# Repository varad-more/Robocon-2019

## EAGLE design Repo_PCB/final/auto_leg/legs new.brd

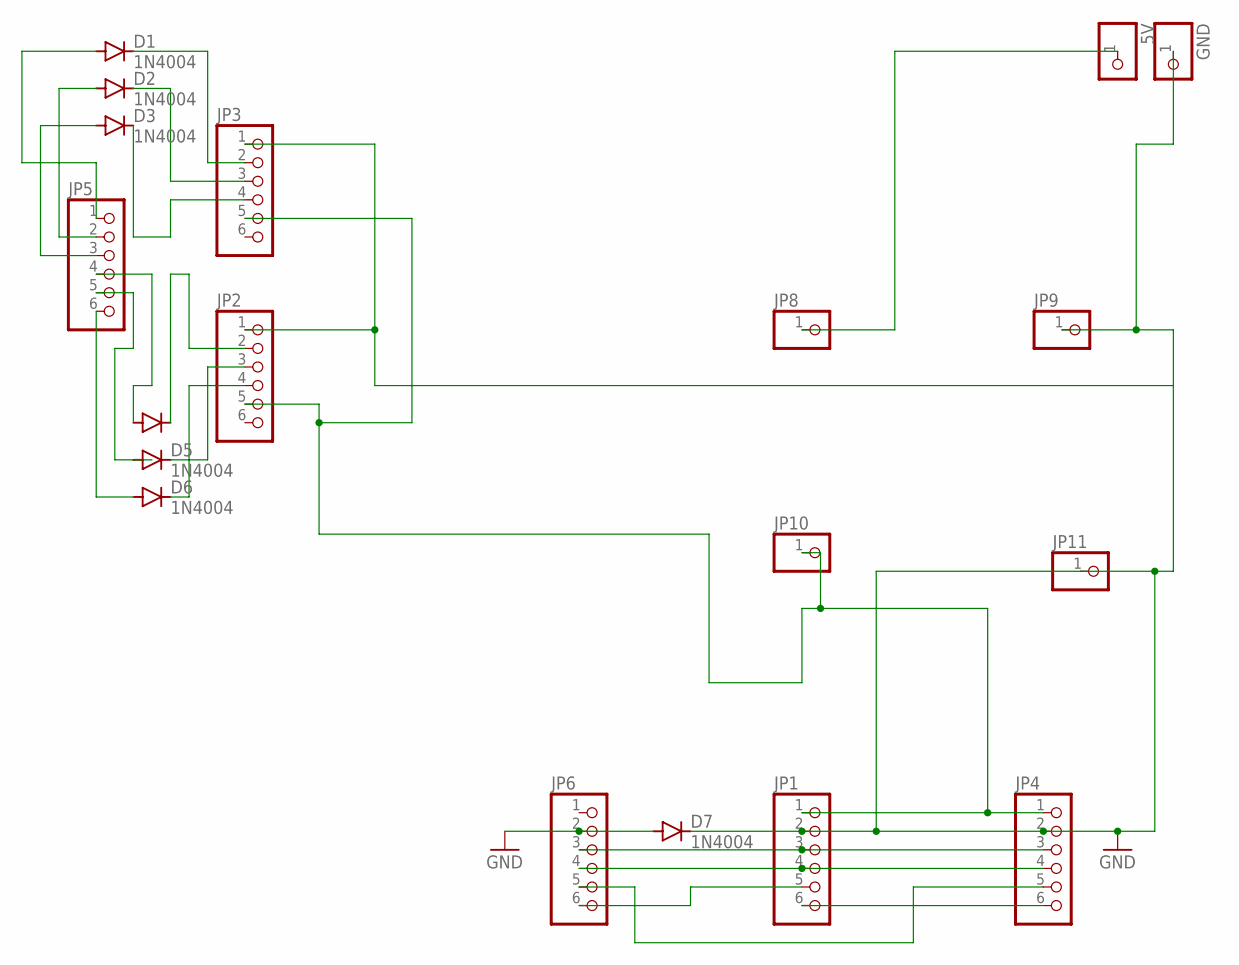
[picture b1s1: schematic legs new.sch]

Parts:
5V: PINHD-1X1; 1X01
D1, D2, D3, D4, D5, D6, D7: 1N4004; DO41-10
GND: PINHD-1X1; 1X01
JP1, JP2, JP3, JP4, JP5, JP6: PINHD-1X6; 1X06
JP8, JP9, JP10, JP11: PINHD-1X1; 1X01

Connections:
GND: D7.A, D7.C, GND.1, JP1.2, JP2.1, JP3.1, JP4.2, JP6.2, JP9.1, JP11.1
unnamed: 5V.1, JP8.1
unnamed: D1.A, JP5.1
unnamed: D2.A, JP5.2
unnamed: JP1.4, JP4.4, JP6.4
unnamed: D3.C, JP3.4
unnamed: JP1.6, JP4.6
unnamed: D4.C, JP2.2
unnamed: D5.A, JP5.5
unnamed: D6.A, JP5.6
unnamed: JP4.5, JP6.5
unnamed: JP1.3, JP4.3, JP6.3
unnamed: JP1.5, JP6.6
unnamed: D4.A, JP5.4
unnamed: D6.C, JP2.4
unnamed: D5.C, JP2.3
unnamed: D1.C, JP3.2
unnamed: D3.A, JP5.3
unnamed: D2.C, JP3.3
VCC: JP1.1, JP2.5, JP3.5, JP4.1, JP10.1

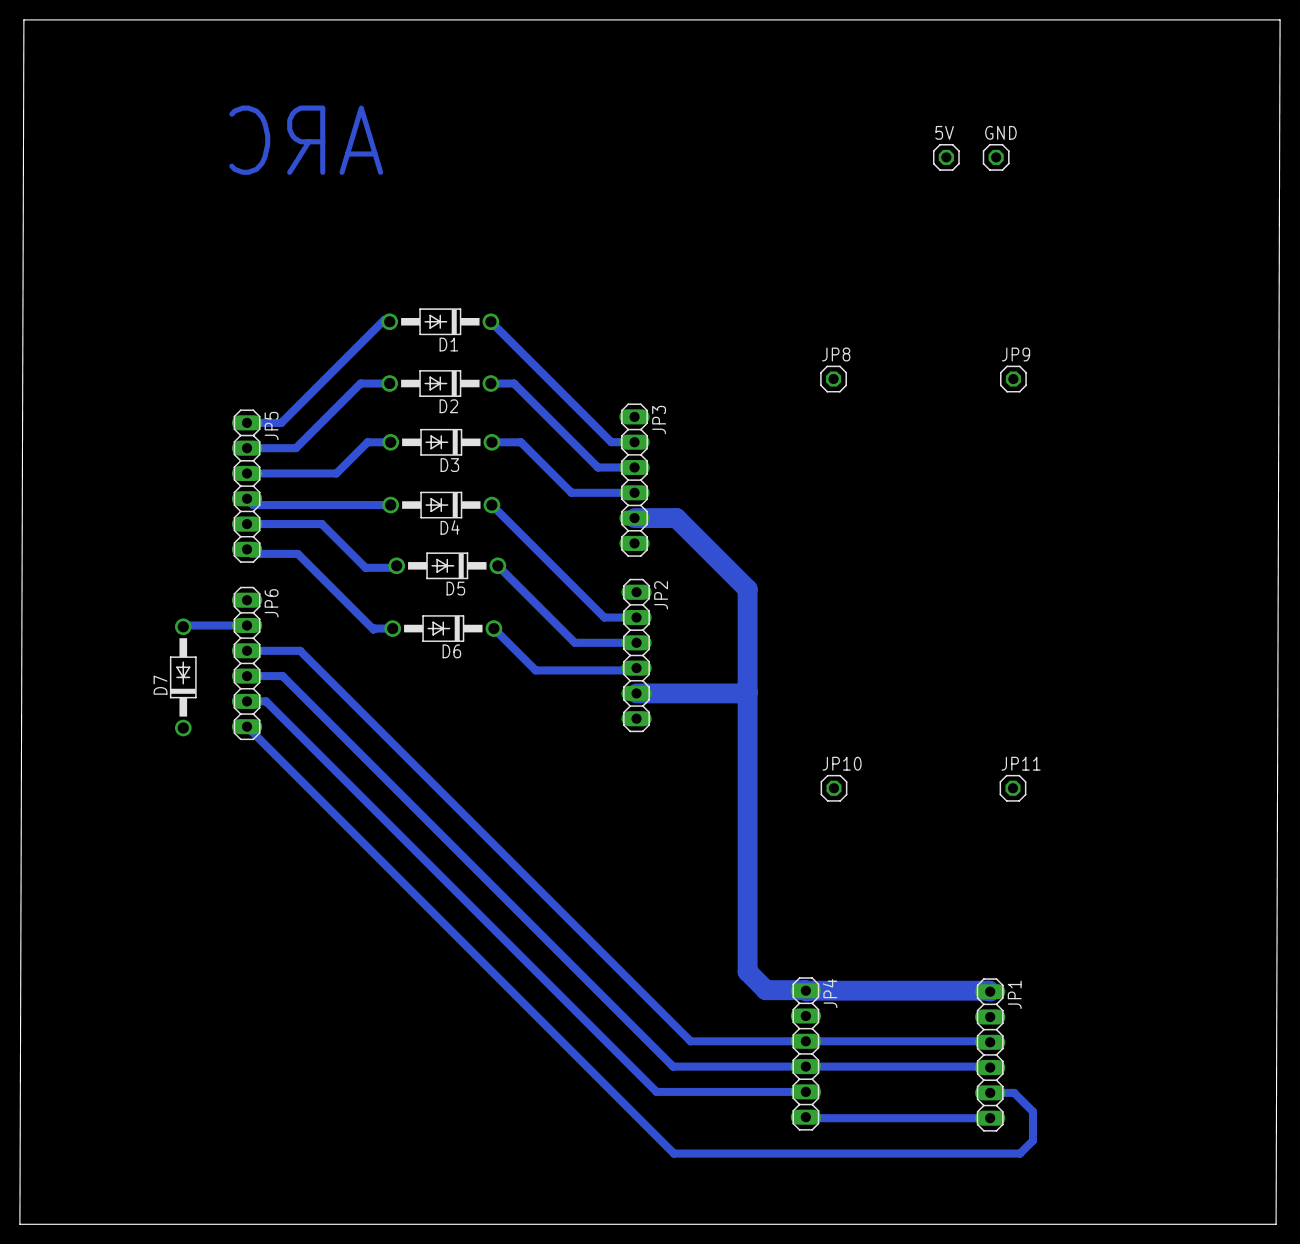
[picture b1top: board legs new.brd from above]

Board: 2 copper layers, 126.5 x 120.9 mm, 19 parts (0 on the bottom side), 20 nets.

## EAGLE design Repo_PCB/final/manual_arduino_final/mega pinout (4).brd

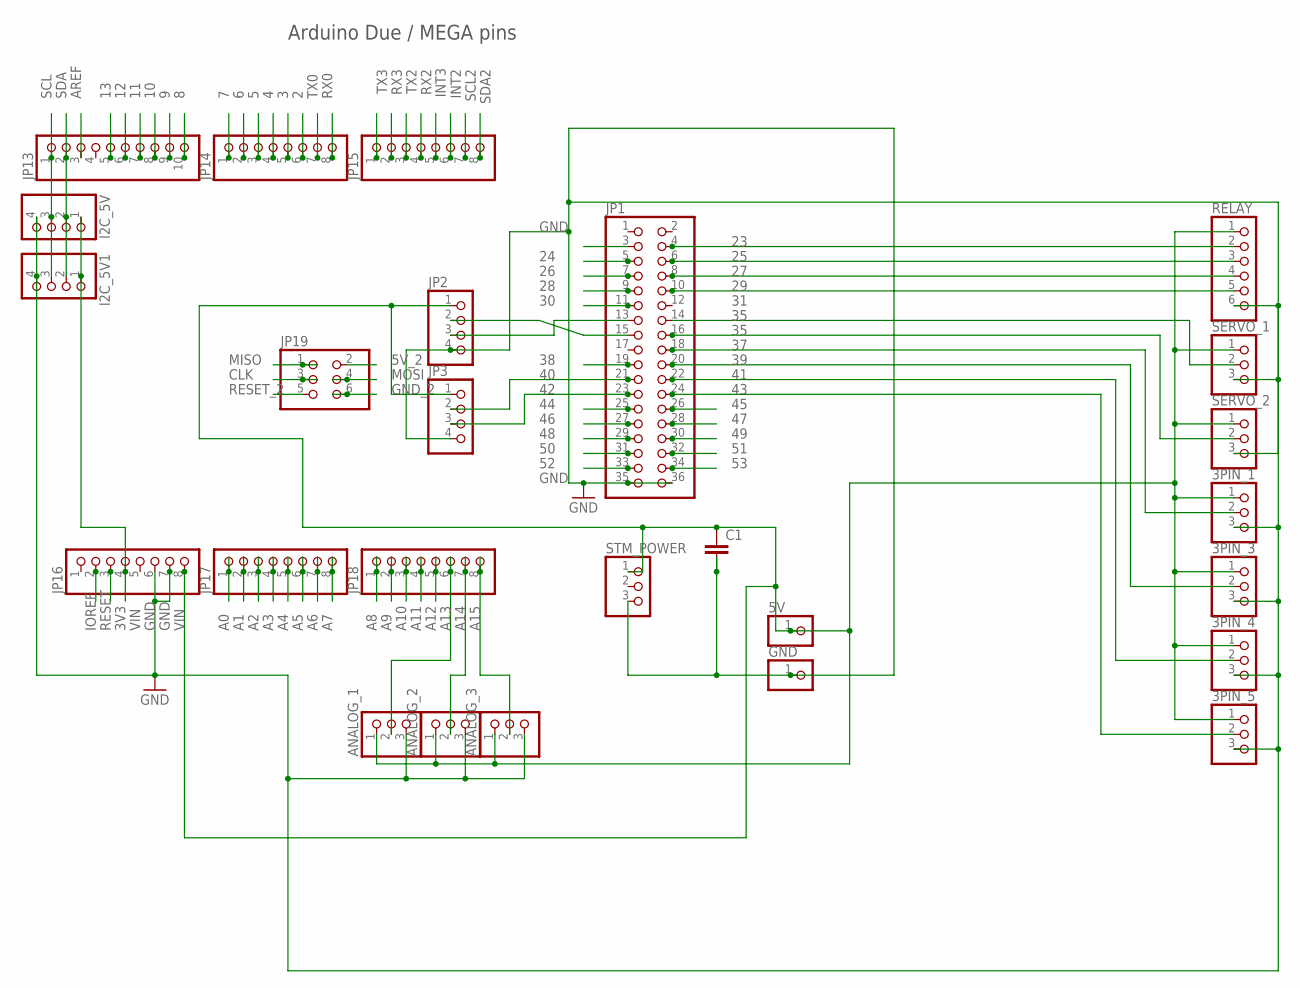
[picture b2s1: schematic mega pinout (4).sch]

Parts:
3PIN_1, 3PIN_3, 3PIN_4, 3PIN_5: PINHD-1X3; 1X03
5V: PINHD-1X1; 1X01
ANALOG_1, ANALOG_2, ANALOG_3: PINHD-1X3; 1X03
C1: C-EU075-032X103; C075-032X103
GND: PINHD-1X1; 1X01
I2C_5V, I2C_5V1: PINHD-1X4; 1X04
JP1: PINHD-2X18; 2X18
JP2, JP3: PINHD-1X4; 1X04
JP13: PINHD-1X10; 1X10
JP14, JP15, JP16, JP17, JP18: PINHD-1X8; 1X08
JP19: PINHD-2X3; 2X03
RELAY: PINHD-1X6; 1X06
SERVO_1, SERVO_2: PINHD-1X3; 1X03
STM_POWER: PINHD-1X3; 1X03

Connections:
2: JP14.6
3: JP14.5
3V3: I2C_5V.1, I2C_5V1.1, JP16.4
4: JP14.4
5: JP14.3
5V_2: JP19.2
6: JP14.2
7: JP14.1
8: JP13.10
9: JP13.9
10: JP13.8
11: JP13.7
12: JP13.6
13: JP13.5
23: JP1.4, RELAY.2
24: JP1.5
25: JP1.6, RELAY.3
26: JP1.7
27: JP1.8, RELAY.4
28: JP1.9
29: JP1.10, RELAY.5
30: JP1.11
31: JP1.14, SERVO_1.2
35: JP1.16, SERVO_2.2
37: 3PIN_1.2, JP1.18
38: JP1.19
39: 3PIN_3.2, JP1.20
40: JP1.21, JP3.2
41: 3PIN_4.2, JP1.22
42: JP1.23, JP3.3
43: 3PIN_5.2, JP1.24
44: JP1.25
45: JP1.26
46: JP1.27
47: JP1.28
48: JP1.29
49: JP1.30
50: JP1.31
51: JP1.32
52: JP1.33
53: JP1.34
A0: JP17.1
A1: JP17.2
A2: JP17.3
A3: JP17.4
A4: JP17.5
A5: JP17.6
A6: JP17.7
A7: JP17.8
A8: JP18.1
A9: JP18.2
A10: JP18.3
A11: JP18.4
A12: JP18.5
A13: ANALOG_1.2, JP18.6
A14: ANALOG_2.2, JP18.7
A15: ANALOG_3.2, JP18.8
AREF: JP13.3
CLK: JP19.3
GND: 3PIN_1.3, 3PIN_3.3, 3PIN_4.3, 3PIN_5.3, ANALOG_1.3, ANALOG_2.3, ANALOG_3.3, C1.2, GND.1, I2C_5V.4, I2C_5V1.4, JP1.35, JP1.36, JP2.4, JP3.4, JP16.6, JP16.7, RELAY.6, SERVO_1.3, SERVO_2.3, STM_POWER.3
GND_2: JP19.6
INT2: JP15.6
INT3: JP15.5
IOREF: JP16.2
MISO: JP19.1
MOSI: JP19.4
unnamed: JP1.15, JP2.2
unnamed: JP1.13, JP2.3
RESET: JP16.3
RESET_2: JP19.5
RX0: JP14.8
RX2: JP15.4
RX3: JP15.2
SCL: I2C_5V.3, I2C_5V1.3, JP13.1
SCL2: JP15.7
SDA: I2C_5V.2, I2C_5V1.2, JP13.2
SDA2: JP15.8
TX0: JP14.7
TX2: JP15.3
TX3: JP15.1
VIN: 3PIN_1.1, 3PIN_3.1, 3PIN_4.1, 3PIN_5.1, 5V.1, ANALOG_1.1, ANALOG_2.1, ANALOG_3.1, C1.1, JP2.1, JP3.1, JP16.8, RELAY.1, SERVO_1.1, SERVO_2.1, STM_POWER.1

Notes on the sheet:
Arduino Due / MEGA pins

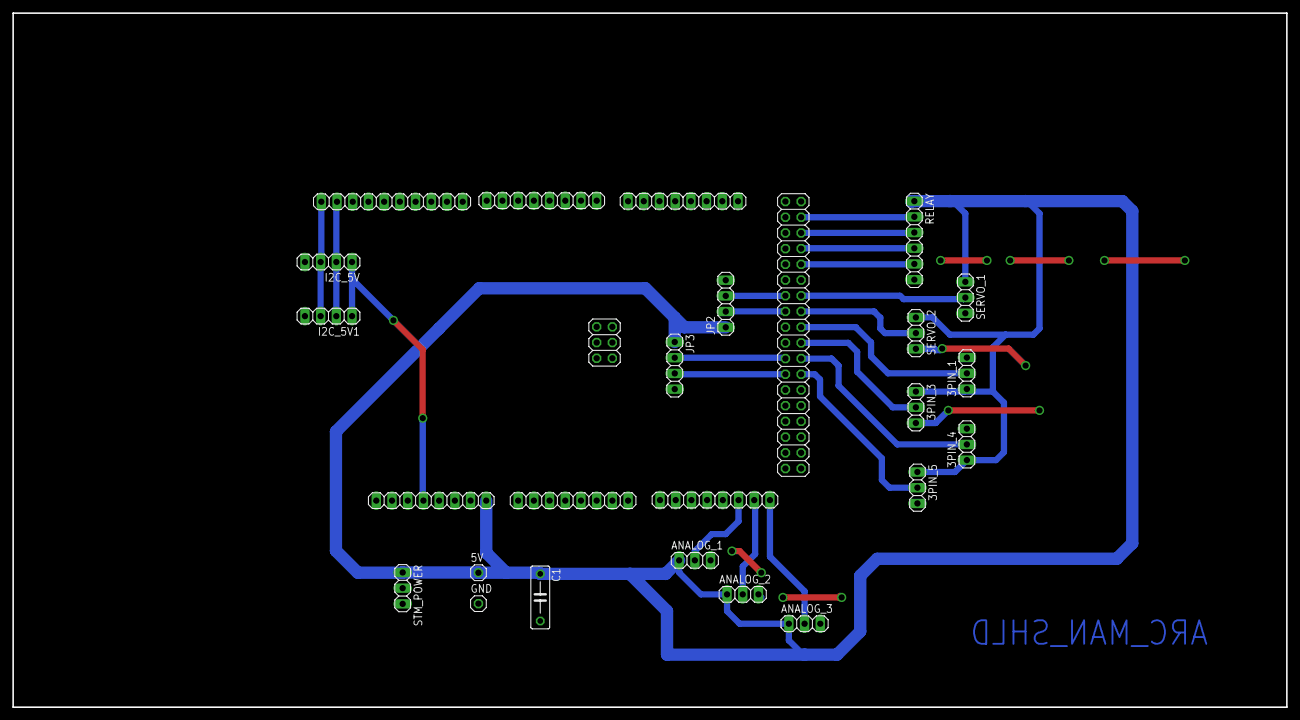
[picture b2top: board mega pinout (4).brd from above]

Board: 2 copper layers, 206.0 x 112.2 mm, 26 parts (0 on the bottom side), 22 nets.

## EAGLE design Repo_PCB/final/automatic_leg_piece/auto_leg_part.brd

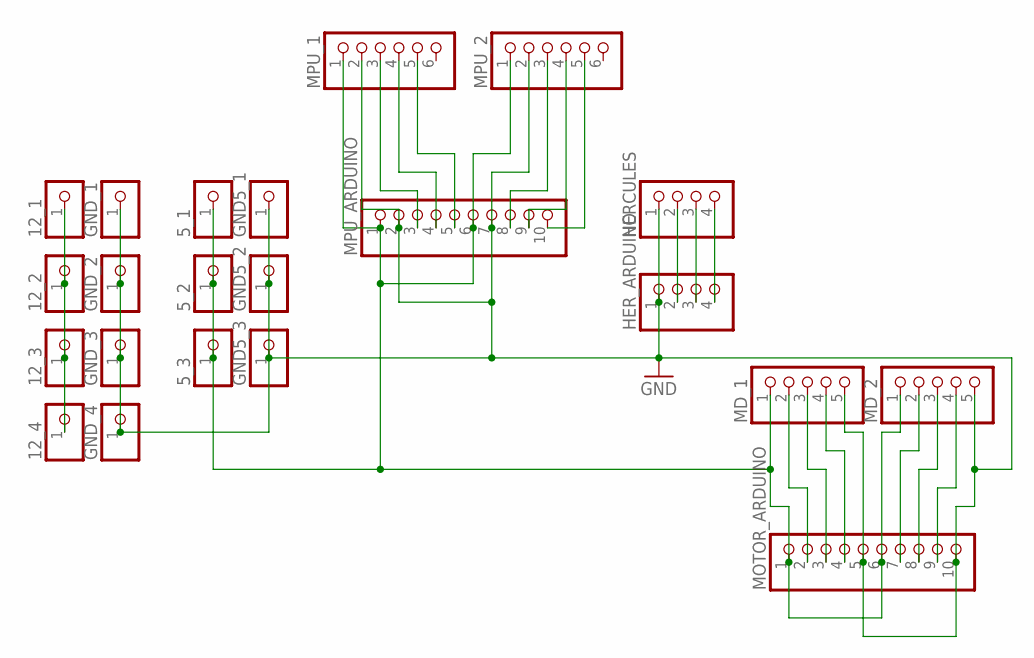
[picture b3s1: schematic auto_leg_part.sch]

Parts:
5_1, 5_2, 5_3, 12_1, 12_2, 12_3, 12_4: PINHD-1X1; 1X01
GND5_1, GND5_2, GND5_3: PINHD-1X1; 1X01
GND_1, GND_2, GND_3, GND_4: PINHD-1X1; 1X01
HERCULES: PINHD-1X4; 1X04
HER_ARDUINO: PINHD-1X4; 1X04
MD_1, MD_2: PINHD-1X5; 1X05
MOTOR_ARDUINO: PINHD-1X10; 1X10
MPU_1, MPU_2: PINHD-1X6; 1X06
MPU_ARDUINO: PINHD-1X10; 1X10

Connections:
GND: GND5_1.1, GND5_2.1, GND5_3.1, GND_1.1, GND_2.1, GND_3.1, GND_4.1, HERCULES.1, HER_ARDUINO.1, MD_1.5, MD_2.5, MOTOR_ARDUINO.5, MOTOR_ARDUINO.10, MPU_1.2, MPU_2.2, MPU_ARDUINO.2, MPU_ARDUINO.7
unnamed: 12_1.1, 12_2.1, 12_3.1, 12_4.1
unnamed: 5_1.1, 5_2.1, 5_3.1, MD_1.1, MD_2.1, MOTOR_ARDUINO.1, MOTOR_ARDUINO.6, MPU_1.1, MPU_2.1, MPU_ARDUINO.1, MPU_ARDUINO.6
unnamed: MPU_1.3, MPU_ARDUINO.3
unnamed: MPU_1.4, MPU_ARDUINO.4
unnamed: MPU_1.5, MPU_ARDUINO.5
unnamed: MPU_2.3, MPU_ARDUINO.8
unnamed: MPU_2.4, MPU_ARDUINO.9
unnamed: MPU_2.5, MPU_ARDUINO.10
unnamed: MD_1.4, MOTOR_ARDUINO.4
unnamed: MD_1.3, MOTOR_ARDUINO.3
unnamed: MD_1.2, MOTOR_ARDUINO.2
unnamed: MD_2.2, MOTOR_ARDUINO.7
unnamed: MD_2.3, MOTOR_ARDUINO.8
unnamed: MD_2.4, MOTOR_ARDUINO.9
unnamed: HERCULES.2, HER_ARDUINO.2
unnamed: HERCULES.3, HER_ARDUINO.3
unnamed: HERCULES.4, HER_ARDUINO.4

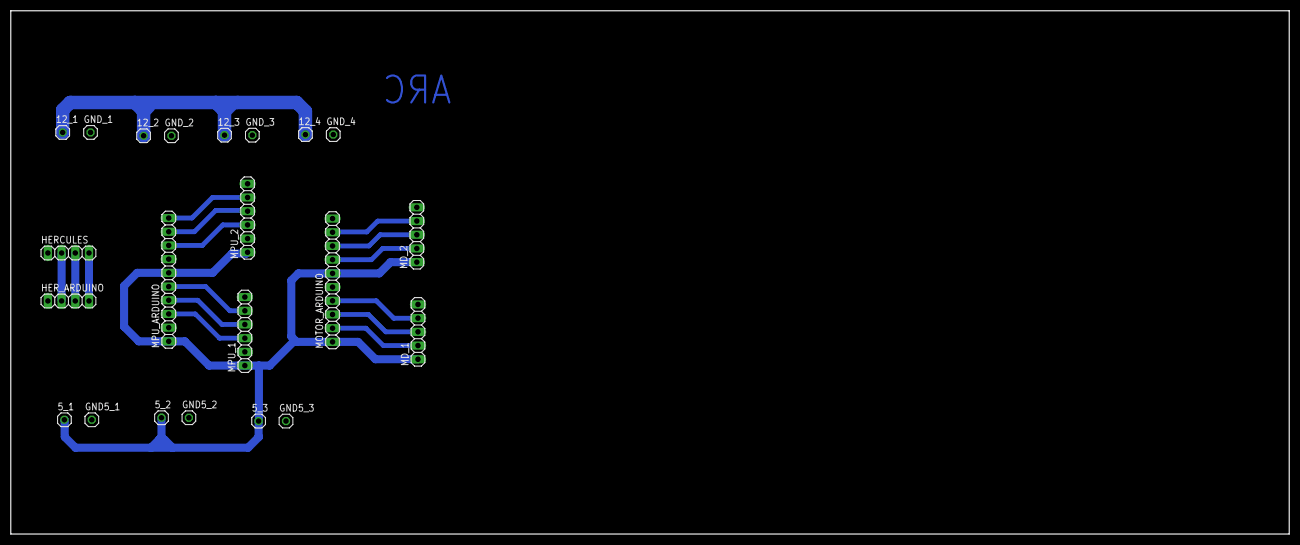
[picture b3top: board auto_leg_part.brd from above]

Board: 2 copper layers, 237.0 x 97.0 mm, 22 parts (0 on the bottom side), 18 nets.

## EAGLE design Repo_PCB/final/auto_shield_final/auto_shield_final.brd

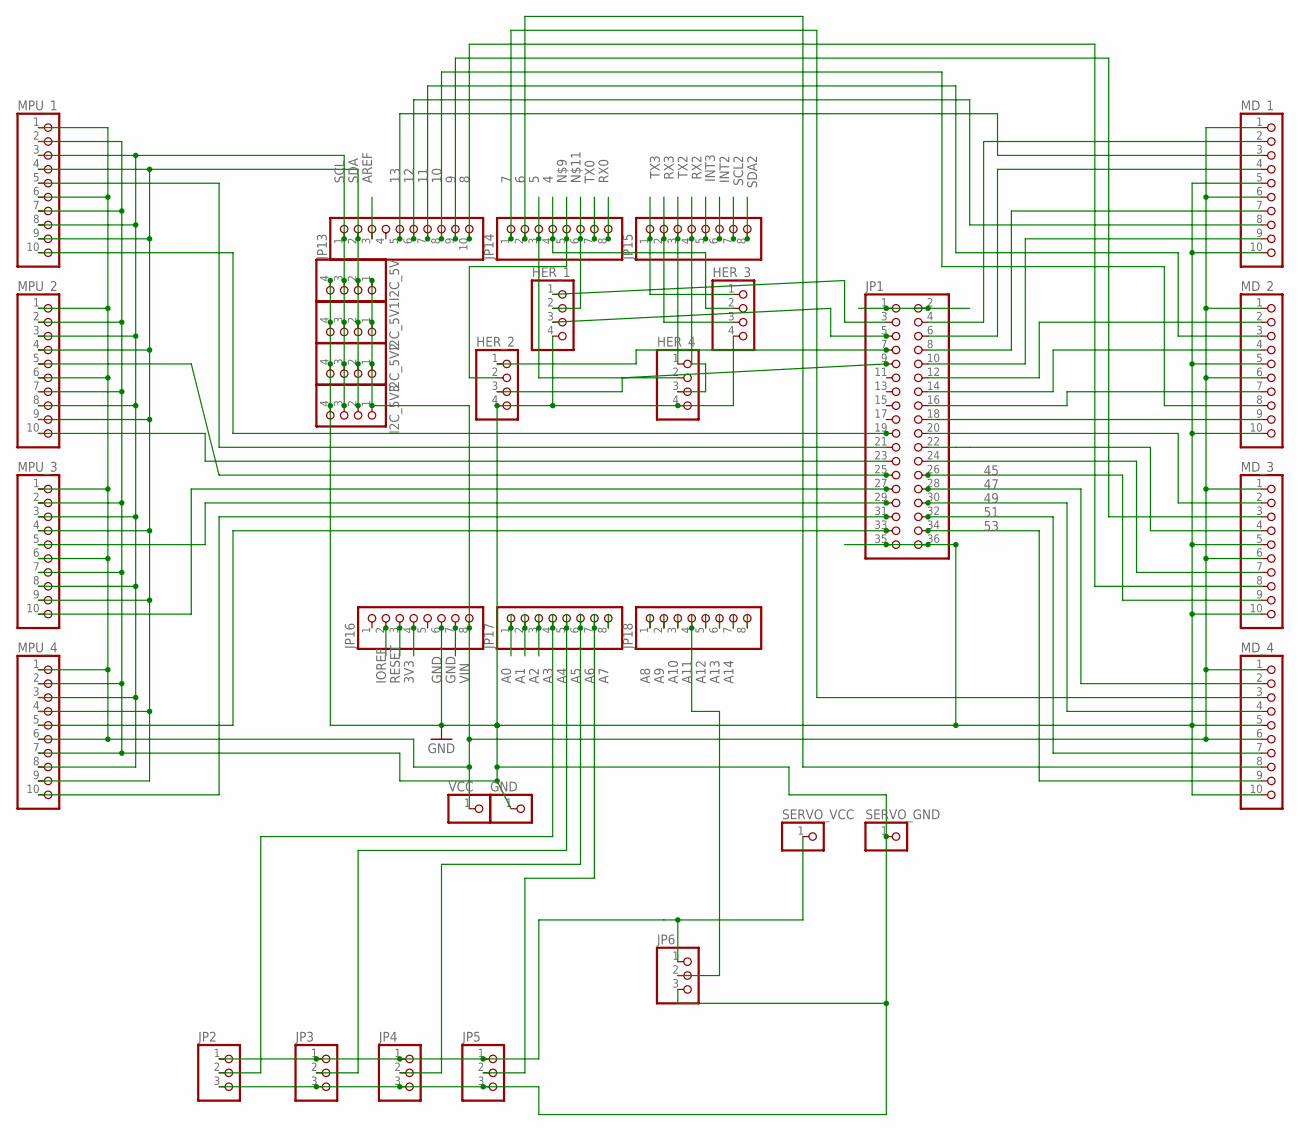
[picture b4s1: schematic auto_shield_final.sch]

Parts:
GND: PINHD-1X1; 1X01
HER_1, HER_2, HER_3, HER_4: PINHD-1X4; 1X04
I2C_5V, I2C_5V1, I2C_5V2, I2C_5V3: PINHD-1X4; 1X04
JP1: PINHD-2X18; 2X18
JP2, JP3, JP4, JP5, JP6: PINHD-1X3; 1X03
JP13: PINHD-1X10; 1X10
JP14, JP15, JP16, JP17, JP18: PINHD-1X8; 1X08
MD_1, MD_2, MD_3, MD_4: PINHD-1X10; 1X10
MPU_1, MPU_2, MPU_3, MPU_4: PINHD-1X10; 1X10
SERVO_GND: PINHD-1X1; 1X01
SERVO_VCC: PINHD-1X1; 1X01
VCC: PINHD-1X1; 1X01

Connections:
3V3: JP16.4
4: HER_3.2, JP14.4
5: HER_4.2, JP14.3
6: JP14.2, MD_4.8
7: JP14.1, MD_4.3
8: JP13.10, MD_3.8
9: JP13.9, MD_3.3
10: JP13.8, MD_2.8
11: JP13.7, MD_2.3
12: JP13.6, MD_1.8
13: JP13.5, MD_1.3
24: HER_1.3, JP1.5
26: HER_2.1, JP1.7
28: HER_2.3, JP1.9
38: JP1.19, MPU_1.10
44: JP1.25, MPU_2.5
45: JP1.26, MD_3.9
46: JP1.27, MPU_3.10
47: JP1.28, MD_4.2
48: JP1.29, MPU_3.5
49: JP1.30, MD_4.4
50: JP1.31, MPU_4.10
51: JP1.32, MD_4.7
52: JP1.33, MPU_4.5
53: JP1.34, MD_4.9
A0: JP17.1
A1: JP17.2
A2: JP17.3
A3: JP2.2, JP17.4
A4: JP3.2, JP17.5
A5: JP4.2, JP17.6
A6: JP5.2, JP17.7
A7: JP17.8
A8: JP18.1
A9: JP18.2
A10: JP18.3
A11: JP6.2, JP18.4
A12: JP18.5
A13: JP18.6
A14: JP18.7
AREF: JP13.3
GND: GND.1, HER_1.4, HER_2.4, HER_3.4, HER_4.4, I2C_5V.4, I2C_5V1.4, I2C_5V2.4, I2C_5V3.4, JP1.35, JP1.36, JP2.3, JP3.3, JP4.3, JP5.3, JP6.3, JP16.6, JP16.7, MD_1.5, MD_1.10, MD_2.5, MD_2.10, MD_3.5, MD_3.10, MD_4.5, MD_4.10, MPU_1.2, MPU_1.7, MPU_2.2, MPU_2.7, MPU_3.2, MPU_3.7, MPU_4.2, MPU_4.7, SERVO_GND.1
INT2: JP15.6
INT3: JP15.5
IOREF: JP16.2
unnamed: HER_1.1, JP1.3
unnamed: JP1.1, JP1.2
unnamed: JP1.4, MD_1.2
unnamed: JP2.1, JP3.1, JP4.1, JP5.1, JP6.1, SERVO_VCC.1
unnamed: JP1.6, MD_1.4
unnamed: JP1.8, MD_1.7
unnamed: JP1.10, MD_1.9
unnamed: HER_2.2, JP14.5
unnamed: HER_1.2, JP14.6
unnamed: JP1.14, MD_2.4
unnamed: JP1.12, MD_2.2
unnamed: JP1.16, MD_2.7
unnamed: JP1.18, MD_2.9
unnamed: JP1.20, MD_3.2
unnamed: JP1.22, MD_3.4
unnamed: JP1.24, MD_3.7
unnamed: JP1.21, MPU_1.5
unnamed: JP1.23, MPU_2.10
RESET: JP16.3
RX0: JP14.8
RX2: HER_4.3, JP15.4
RX3: HER_3.3, JP15.2
SCL: I2C_5V.3, I2C_5V1.3, I2C_5V2.3, I2C_5V3.3, JP13.1, MPU_1.3, MPU_1.8, MPU_2.3, MPU_2.8, MPU_3.3, MPU_3.8, MPU_4.3, MPU_4.8
SCL2: JP15.7
SDA: I2C_5V.2, I2C_5V1.2, I2C_5V2.2, I2C_5V3.2, JP13.2, MPU_1.4, MPU_1.9, MPU_2.4, MPU_2.9, MPU_3.4, MPU_3.9, MPU_4.4, MPU_4.9
SDA2: JP15.8
TX0: JP14.7
TX2: HER_4.1, JP15.3
TX3: HER_3.1, JP15.1
VIN: I2C_5V.1, I2C_5V1.1, I2C_5V2.1, I2C_5V3.1, JP16.8, MD_1.1, MD_1.6, MD_2.1, MD_2.6, MD_3.1, MD_3.6, MD_4.1, MD_4.6, MPU_1.1, MPU_1.6, MPU_2.1, MPU_2.6, MPU_3.1, MPU_3.6, MPU_4.1, MPU_4.6, VCC.1

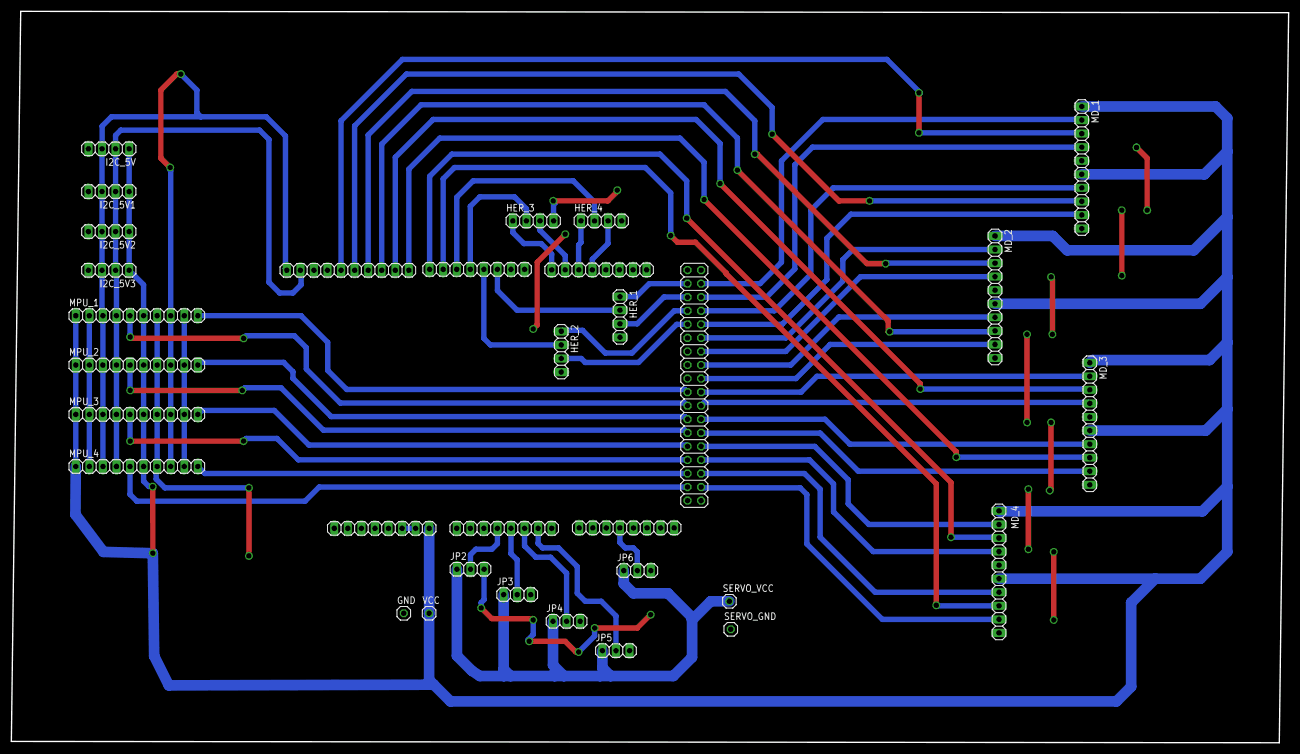
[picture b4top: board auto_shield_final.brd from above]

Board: 2 copper layers, 239.2 x 137.0 mm, 32 parts (0 on the bottom side), 55 nets.

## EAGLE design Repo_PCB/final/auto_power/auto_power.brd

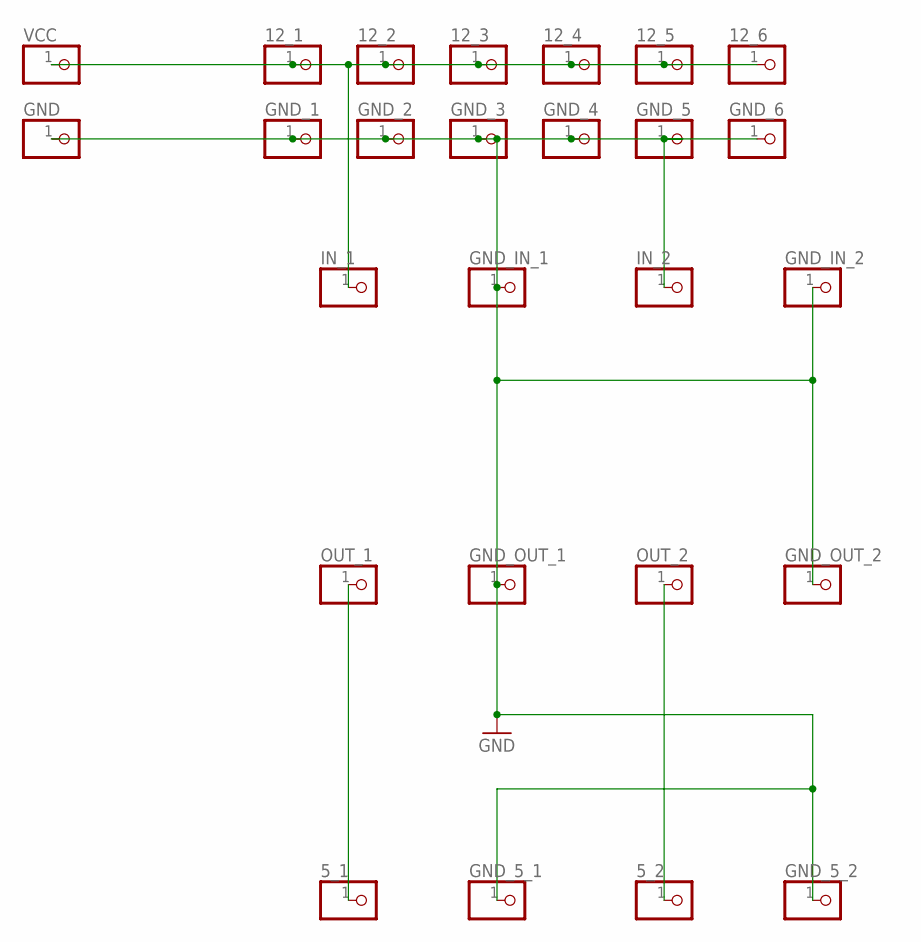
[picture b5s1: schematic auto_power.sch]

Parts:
5_1, 5_2, 12_1, 12_2, 12_3, 12_4, 12_5, 12_6: PINHD-1X1; 1X01
GND: PINHD-1X1; 1X01
GND_1, GND_2, GND_3, GND_4, GND_5, GND_5_1, GND_5_2, GND_6: PINHD-1X1; 1X01
GND_IN_1, GND_IN_2: PINHD-1X1; 1X01
GND_OUT_1, GND_OUT_2: PINHD-1X1; 1X01
IN_1, IN_2: PINHD-1X1; 1X01
OUT_1, OUT_2: PINHD-1X1; 1X01
VCC: PINHD-1X1; 1X01

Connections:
GND: GND.1, GND_1.1, GND_2.1, GND_3.1, GND_4.1, GND_5.1, GND_5_1.1, GND_5_2.1, GND_6.1, GND_IN_1.1, GND_IN_2.1, GND_OUT_1.1, GND_OUT_2.1, IN_2.1
unnamed: 5_1.1, OUT_1.1
unnamed: 5_2.1, OUT_2.1
unnamed: 12_1.1, 12_2.1, 12_3.1, 12_4.1, 12_5.1, 12_6.1, IN_1.1, VCC.1

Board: 2 copper layers, 26 parts (0 on the bottom side), 4 nets, no tracks yet.

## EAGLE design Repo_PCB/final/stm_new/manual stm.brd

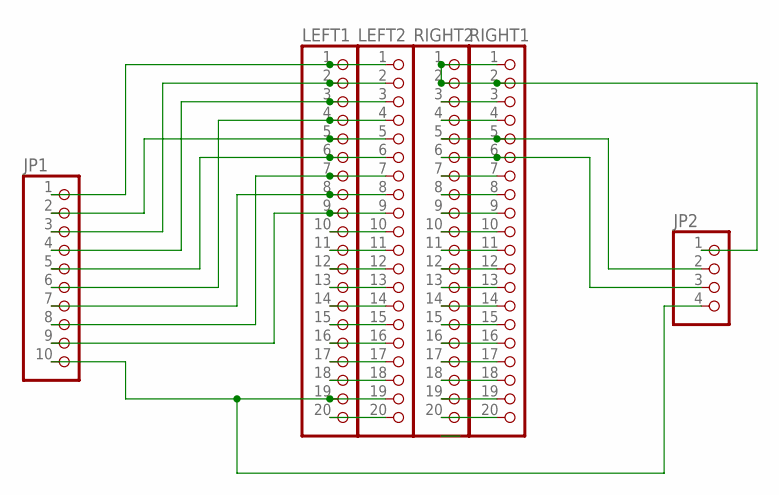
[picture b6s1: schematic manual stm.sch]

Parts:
JP1: PINHD-1X10; 1X10
JP2: PINHD-1X4; 1X04
LEFT1, LEFT2: PINHD-1X20; 1X20
RIGHT1, RIGHT2: PINHD-1X20; 1X20

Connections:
ENCODER4: RIGHT1.4, RIGHT2.4
GND1: JP1.10, JP2.4, LEFT1.19, LEFT2.19
unnamed: LEFT1.18, LEFT2.18
unnamed: JP2.1, RIGHT1.1, RIGHT1.2, RIGHT2.1, RIGHT2.2
unnamed: JP1.1, LEFT1.1, LEFT2.1
unnamed: JP1.3, LEFT1.2, LEFT2.2
unnamed: JP1.4, LEFT1.3, LEFT2.3
unnamed: JP1.6, LEFT1.4, LEFT2.4
unnamed: JP1.2, LEFT1.5, LEFT2.5
unnamed: RIGHT1.10, RIGHT2.10
unnamed: RIGHT1.9, RIGHT2.9
unnamed: JP1.7, LEFT1.8, LEFT2.8
unnamed: JP1.9, LEFT1.9, LEFT2.9
unnamed: LEFT1.10, LEFT2.10
unnamed: LEFT1.11, LEFT2.11
unnamed: RIGHT1.19, RIGHT2.19
unnamed: RIGHT1.18, RIGHT2.18
unnamed: RIGHT1.17, RIGHT2.17
unnamed: RIGHT1.14, RIGHT2.14
unnamed: RIGHT1.15, RIGHT2.15
unnamed: RIGHT1.16, RIGHT2.16
unnamed: LEFT1.12, LEFT2.12
unnamed: RIGHT1.13, RIGHT2.13
unnamed: LEFT1.17, LEFT2.17
unnamed: LEFT1.16, LEFT2.16
unnamed: LEFT1.15, LEFT2.15
unnamed: RIGHT1.7, RIGHT2.7
unnamed: LEFT1.20, LEFT2.20
unnamed: JP1.5, LEFT1.6, LEFT2.6
unnamed: LEFT1.14, LEFT2.14
unnamed: JP1.8, LEFT1.7, LEFT2.7
unnamed: RIGHT1.11, RIGHT2.11
unnamed: RIGHT1.12, RIGHT2.12
unnamed: LEFT1.13, LEFT2.13
unnamed: RIGHT1.3, RIGHT2.3
unnamed: RIGHT1.8, RIGHT2.8
unnamed: JP2.2, RIGHT1.5, RIGHT2.5
unnamed: JP2.3, RIGHT1.6, RIGHT2.6
unnamed: RIGHT1.20, RIGHT2.20

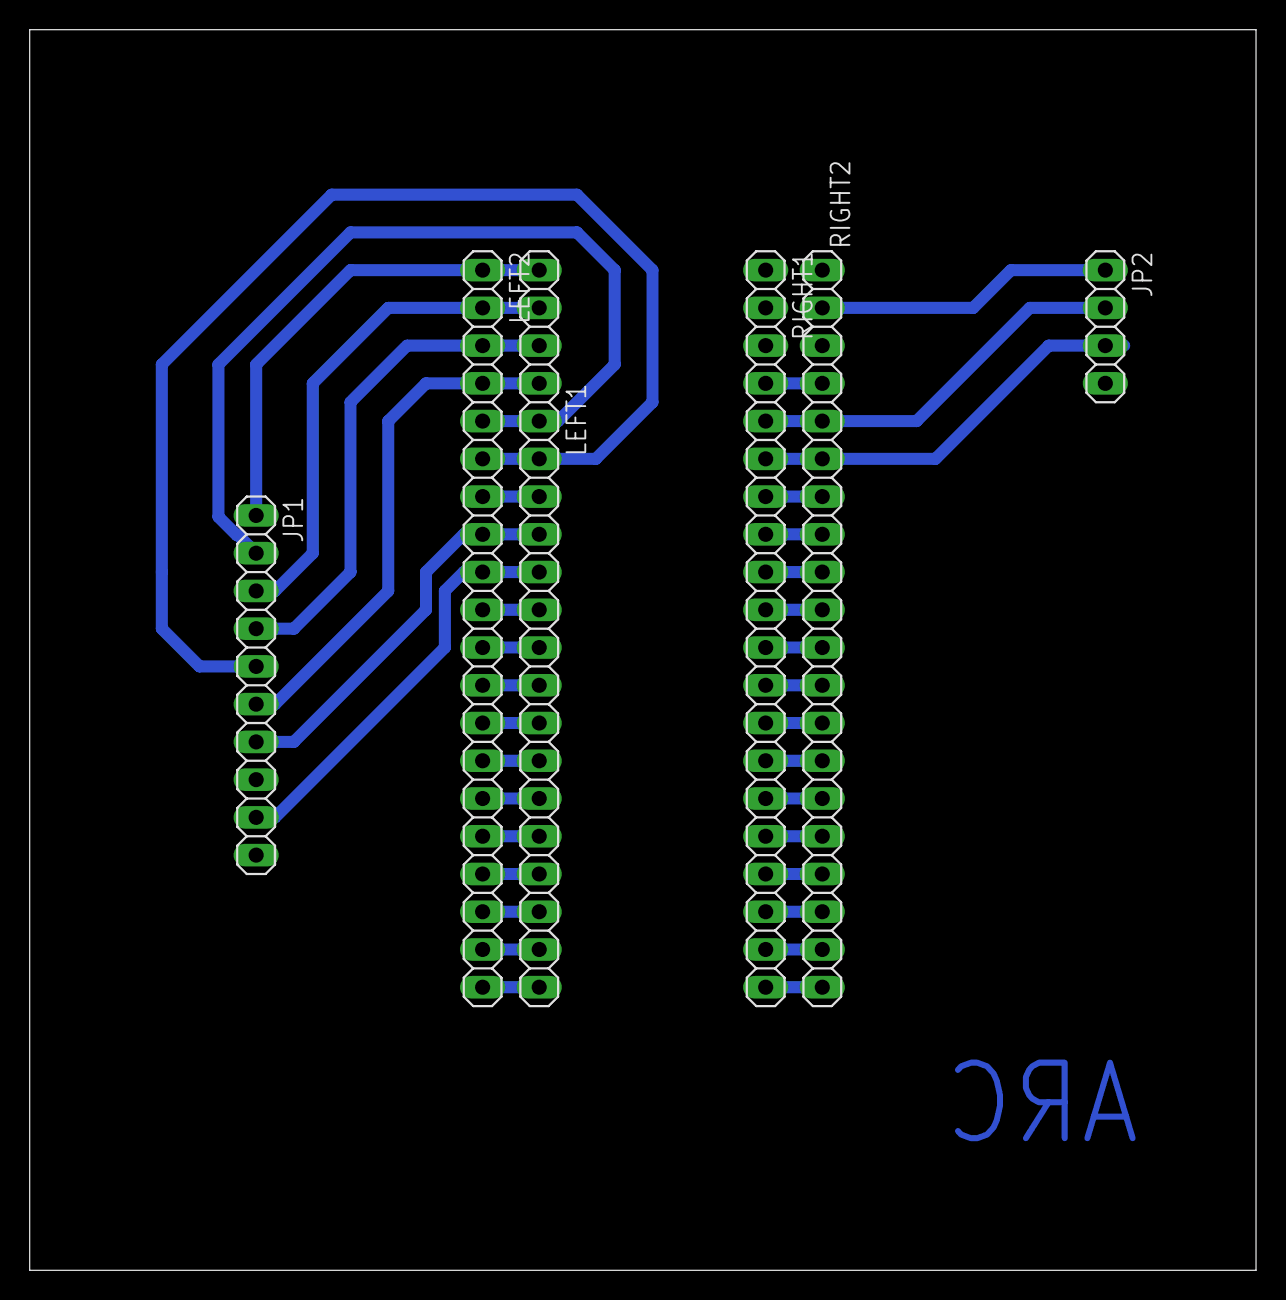
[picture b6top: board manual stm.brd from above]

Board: 2 copper layers, 82.5 x 83.5 mm, 6 parts (0 on the bottom side), 39 nets.

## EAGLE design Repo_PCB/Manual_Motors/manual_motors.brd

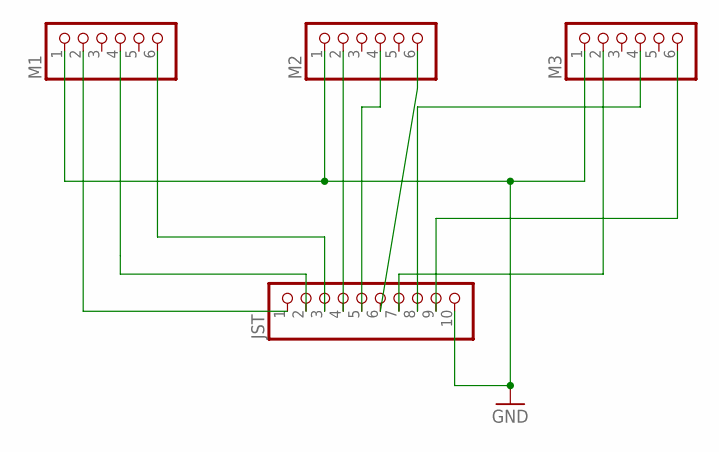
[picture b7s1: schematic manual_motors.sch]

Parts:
JST: PINHD-1X10; 1X10
M1, M2, M3: PINHD-1X6; 1X06

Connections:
GND: JST.10, M1.1, M2.1, M3.1
unnamed: JST.1, M1.2
unnamed: JST.4, M2.2
unnamed: JST.5, M2.4
unnamed: JST.6, M2.6
unnamed: JST.9, M3.6
unnamed: JST.2, M1.4
unnamed: JST.8, M3.4
unnamed: JST.7, M3.2
unnamed: JST.3, M1.6

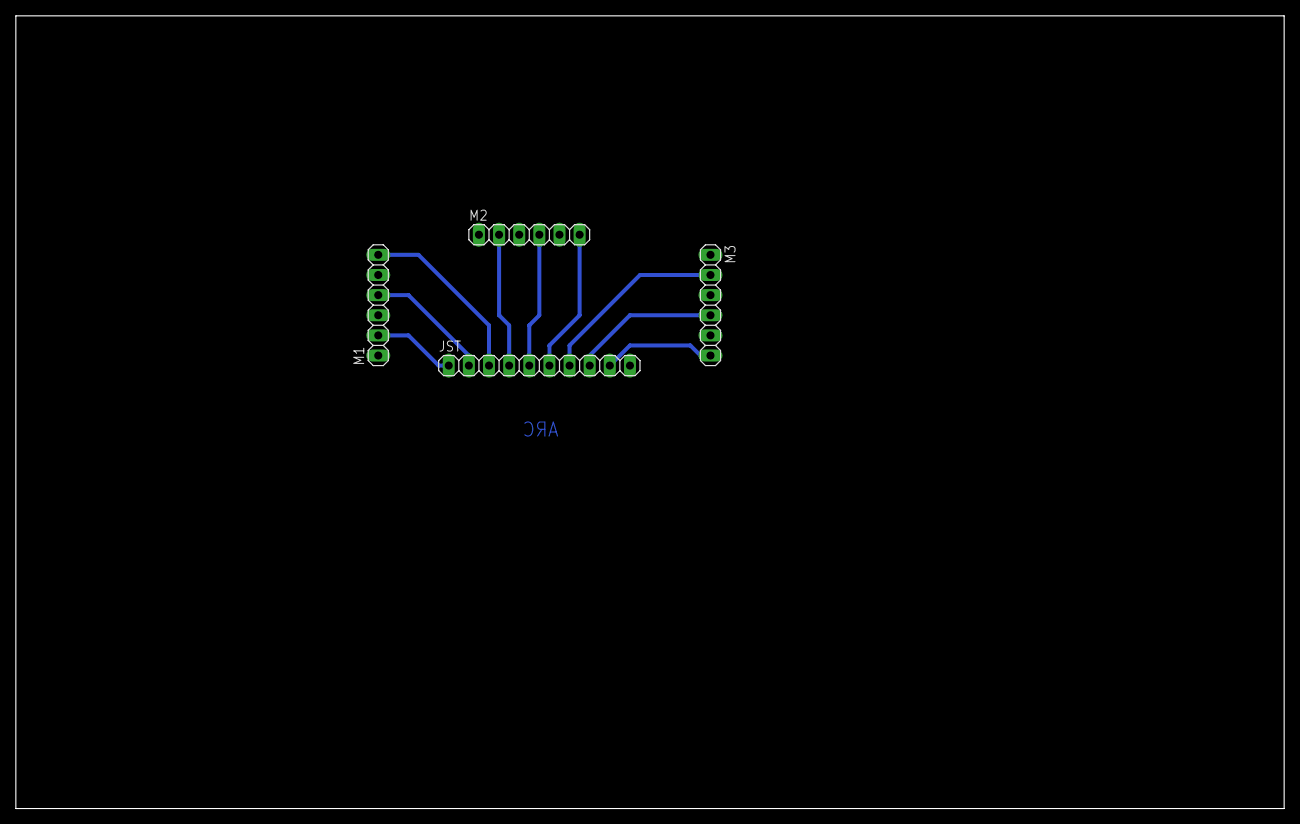
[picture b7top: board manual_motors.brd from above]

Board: 2 copper layers, 160.0 x 100.0 mm, 4 parts (0 on the bottom side), 10 nets.

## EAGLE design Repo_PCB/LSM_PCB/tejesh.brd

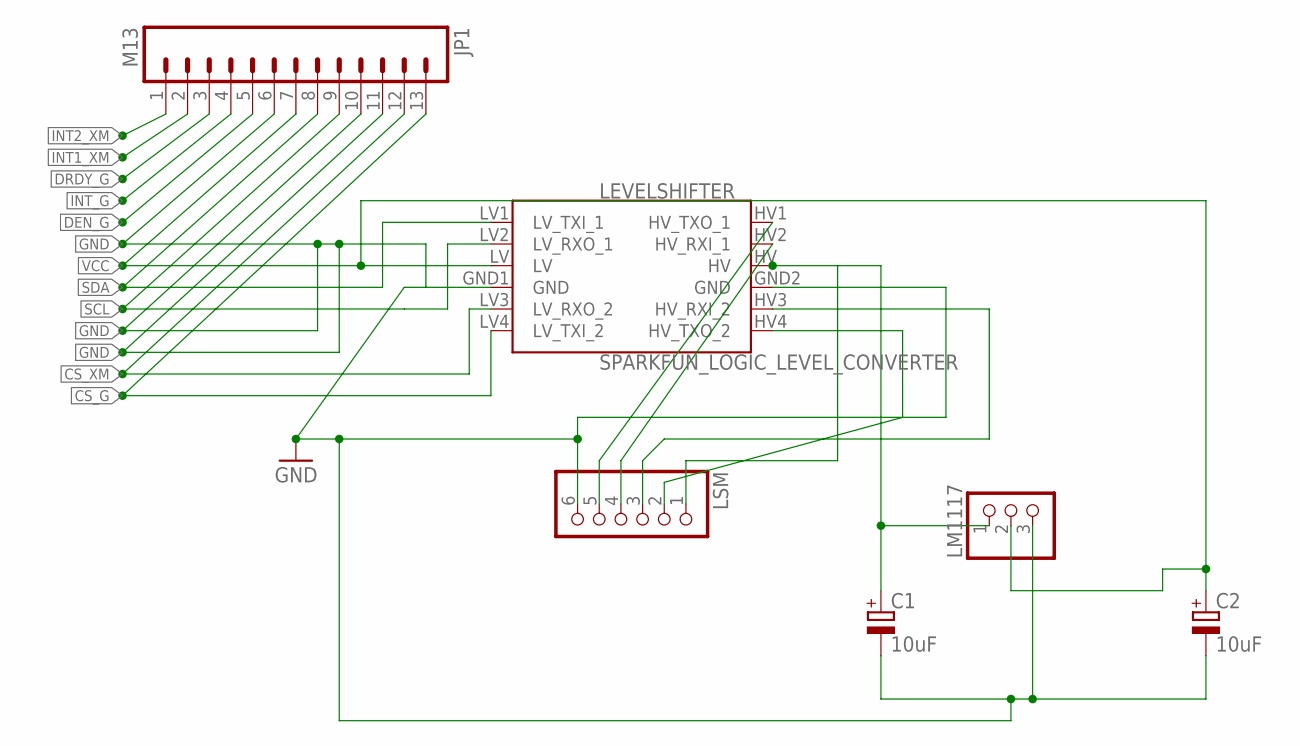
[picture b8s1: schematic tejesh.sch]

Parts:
C1, C2: 10uF; E2,5-6
JP1: M13; 1X13
LEVELSHIFTER: SPARKFUN_LOGIC_LEVEL_CONVERTER
LM1117: PINHD-1X3; 1X03
LSM: PINHD-1X6; 1X06

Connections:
CS_G: JP1.13, LEVELSHIFTER.LV4 (LV_TXI_2)
CS_XM: JP1.12, LEVELSHIFTER.LV3 (LV_RXO_2)
DEN_G: JP1.5
DRDY_G: JP1.3
GND: C1.-, C2.-, JP1.6, JP1.10, JP1.11, LEVELSHIFTER.GND1 (GND), LEVELSHIFTER.GND2 (GND), LM1117.3, LSM.6
INT1_XM: JP1.2
INT2_XM: JP1.1
INT_G: JP1.4
unnamed: C1.+, LEVELSHIFTER.HV, LM1117.1, LSM.1
unnamed: LEVELSHIFTER.HV1 (HV_TXO_1), LSM.5
unnamed: LEVELSHIFTER.HV2 (HV_RXI_1), LSM.4
unnamed: LEVELSHIFTER.HV3 (HV_RXI_2), LSM.3
unnamed: LEVELSHIFTER.HV4 (HV_TXO_2), LSM.2
SCL: JP1.9, LEVELSHIFTER.LV2 (LV_RXO_1)
SDA: JP1.8, LEVELSHIFTER.LV1 (LV_TXI_1)
VCC: C2.+, JP1.7, LEVELSHIFTER.LV, LM1117.2

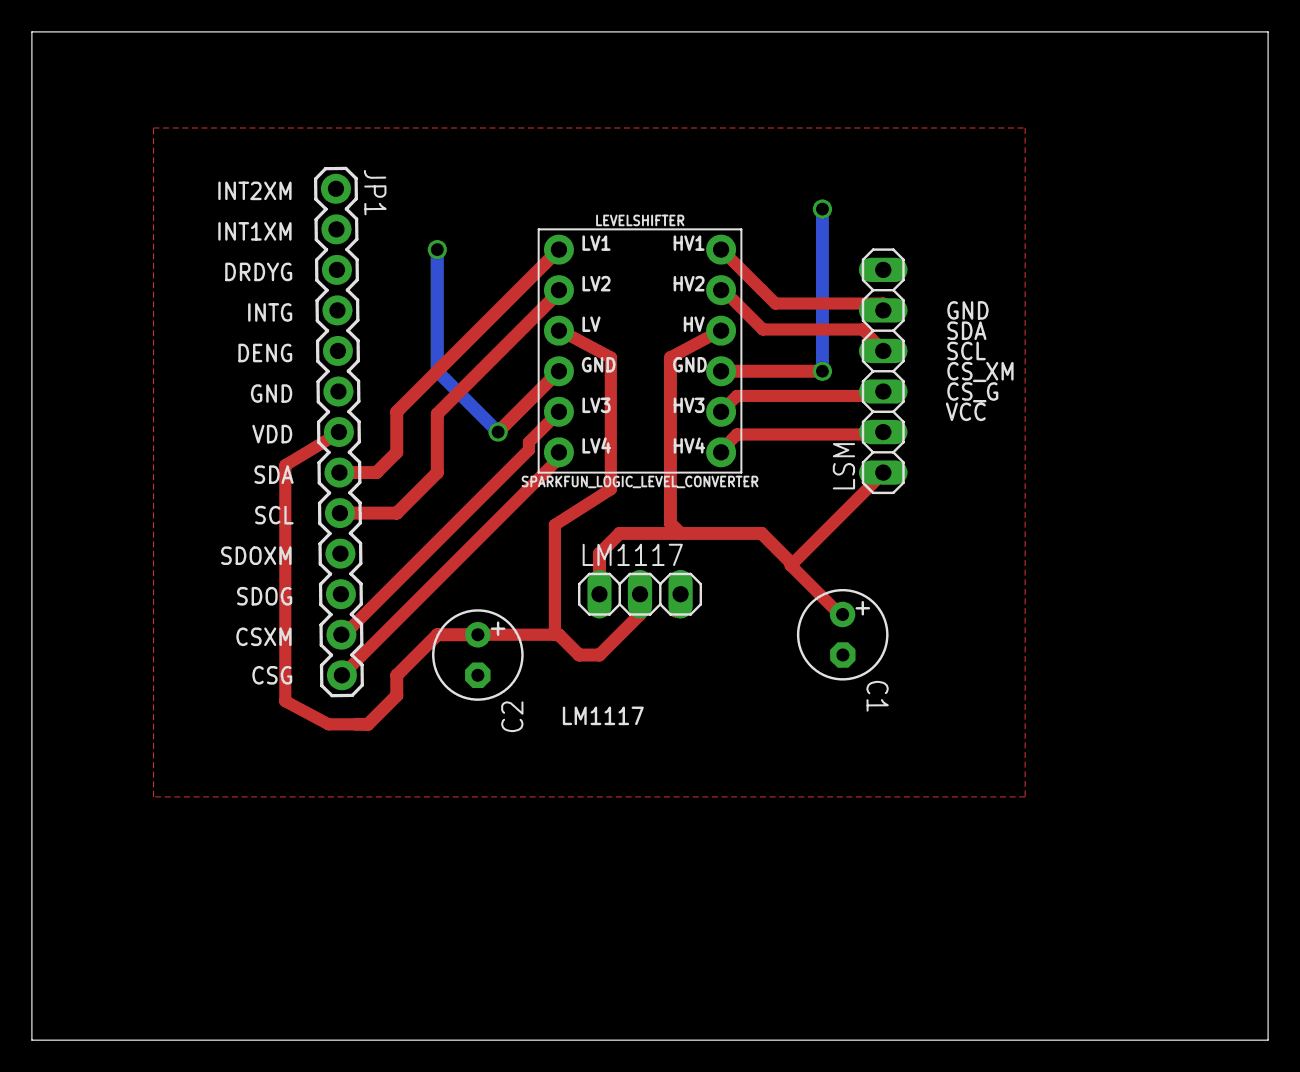
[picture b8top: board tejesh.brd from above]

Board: 2 copper layers, 77.5 x 63.2 mm, 6 parts (0 on the bottom side), 11 nets.

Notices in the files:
parts and their libraries:
SparkFun-Boards: Licensing: Creative Commons ShareAlike 4.0 International - https://creativecommons.org/licenses/by-sa/4.0
SparkFun-Connectors: Licensing: CC v3.0 Share-Alike You are welcome to use this library for commercial purposes.
